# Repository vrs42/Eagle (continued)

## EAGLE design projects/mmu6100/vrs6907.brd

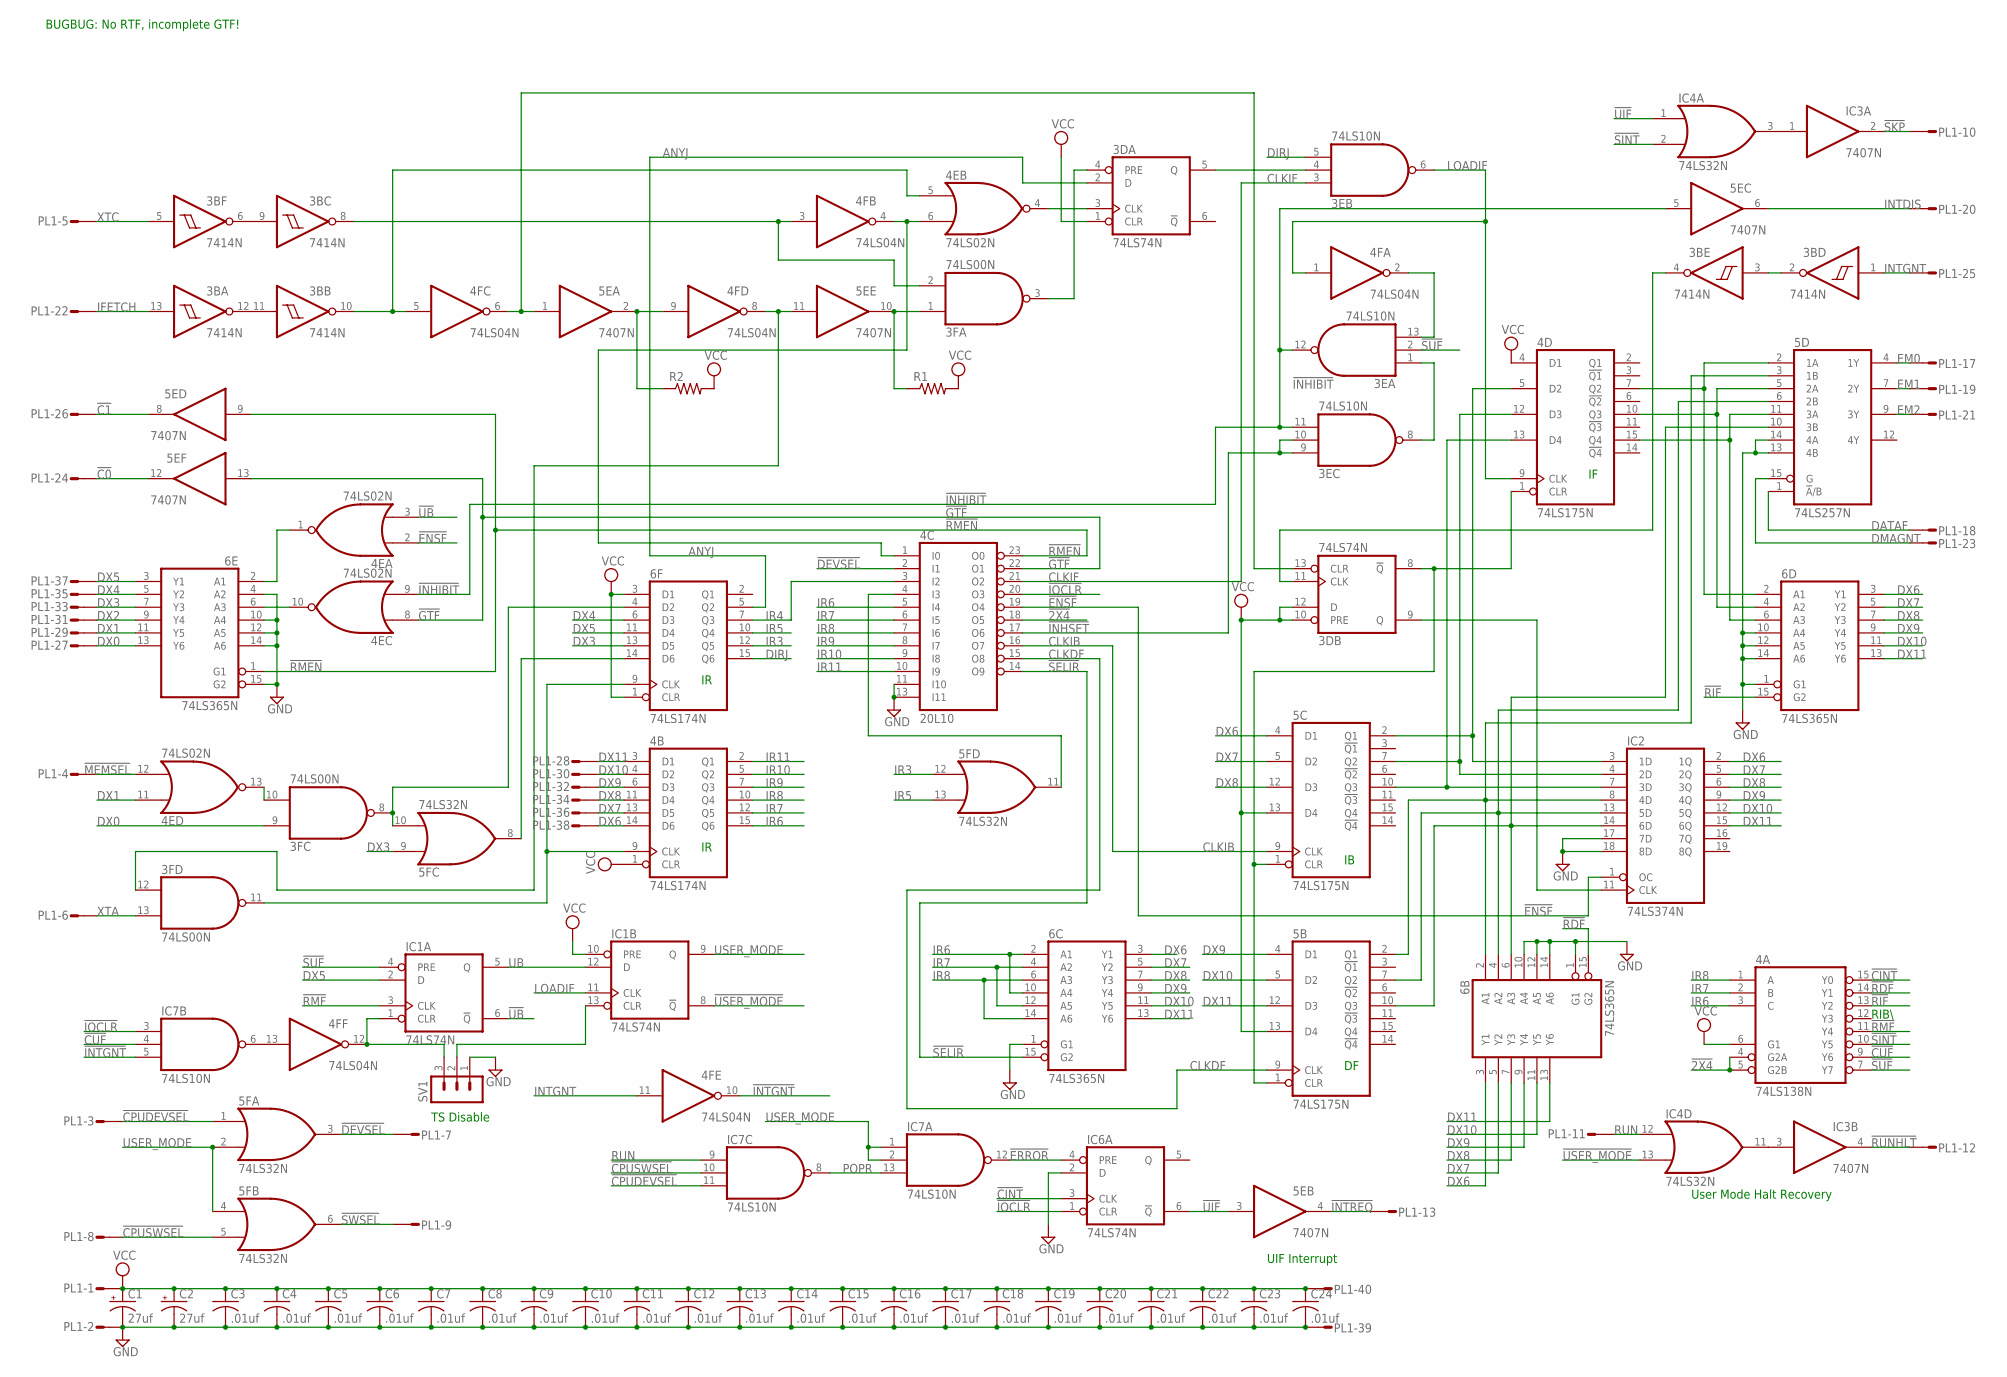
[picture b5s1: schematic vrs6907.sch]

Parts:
3B: 7414N; DIL14
3D: 74LS74N; DIL14
3E: 74LS10N; DIL14
3F: 74LS00N; DIL14
4A: 74LS138N; DIL16
4B, 6F: 74LS174N; DIL16
4C: 20L10; DIL24-3
4D, 5B, 5C: 74LS175N; DIL16
4E: 74LS02N; DIL14
4F: 74LS04N; DIL14
5D: 74LS257N; DIL16
5E: 7407N; DIL14
5F: 74LS32N; DIL14
6B, 6C, 6D, 6E: 74LS365N; DIL16
C1, C2: 27uf; E22-6
C3, C4, C5, C6, C7, C8, C9, C10, C11, C12, C13, C14, C15, C16, C17, C18, C19, C20, C21, C22, C23, C24: .01uf; C050-025X075
IC1, IC6: 74LS74N; DIL14
IC2: 74LS374N; DIL20
IC3: 7407N; DIL14
IC4: 74LS32N; DIL14
IC7: 74LS10N; DIL14
PL1: 40VS; 40V
R1, R2: R-US_0207/10; 0207/10
SV1: MA03-1

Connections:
!2X4: 4A.4 (G2A), 4A.5 (G2B), 4C.18 (O5)
!C0: 5E.12 (O), PL1.24
!C1: 5E.8 (O), PL1.26
!CINT: 4A.15 (Y0), IC6.3 (CLK)
!CPUDEVSEL: 5F.1 (I0), IC7.11 (I2), PL1.3
!CPUSWSEL: 5F.5 (I1), IC7.10 (I1), PL1.8
!CUF: 4A.9 (Y6), IC7.4 (I1)
!DEVSEL: 4C.2 (I1), 5F.3 (O), PL1.7
!ENSF: 4C.19 (O4), 4E.2 (I0), IC2.1 (OC)
!ERROR: IC6.4 (PRE), IC7.12 (O)
!GTF: 4C.22 (O1), 4E.8 (I0), 5E.13 (I)
!INHIBIT: 3E.11 (I2), 3E.12 (O), 4E.9 (I1), 5E.5 (I)
!INHSET: 3E.9 (I0), 3E.10 (I1), 4C.17 (O6)
!INTGNT: 4F.10 (O), IC7.5 (I2)
!INTREQ: 5E.4 (O), PL1.13
!IOCLR: 4C.20 (O3), IC6.1 (CLR), IC7.3 (I0)
!MEMSEL: 4E.12 (I1), PL1.4
!RDF: 4A.14 (Y1), 6B.15 (G2)
!RIF: 4A.13 (Y2), 6D.15 (G2)
!RMEN: 4C.23 (O0), 5E.9 (I), 6E.1 (G1)
!RMF: 4A.11 (Y4), IC1.3 (CLK)
!RUNHLT: IC3.4 (O), PL1.12
!SELIR: 4C.14 (O9), 6C.15 (G2)
!SINT: 4A.10 (Y5), IC4.2 (I1)
!SKP: IC3.2 (O), PL1.10
!SUF: 3E.2 (I1), 4A.7 (Y7), IC1.4 (PRE)
!SWSEL: 5F.6 (O), PL1.9
!UB: 4E.3 (I1), IC1.6 (!Q)
!UIF: 5E.3 (I), IC4.1 (I0), IC6.6 (!Q)
!USER_MODE: IC1.8 (!Q), IC4.13 (I1)
ANYJ: 3D.2 (D), 6F.5 (Q2)
CLKDF: 4C.15 (O8), 5B.9 (CLK)
CLKIB: 4C.16 (O7), 5C.9 (CLK)
CLKIF: 3E.3 (I0), 4C.21 (O2)
DATAF: 5D.1 (!A!/B), PL1.18
DIRJ: 3E.5 (I2), 6F.15 (Q6)
DMAGNT: 5D.15 (G), PL1.23
DX0: 3F.9 (I0), 6E.13 (Y6), PL1.27
DX1: 4E.11 (I0), 6E.11 (Y5), PL1.29
DX2: 6E.9 (Y4), PL1.31
DX3: 5F.9 (I0), 6E.7 (Y3), 6F.13 (D5), PL1.33
DX4: 6E.5 (Y2), 6F.6 (D3), PL1.35
DX5: 6E.3 (Y1), 6F.11 (D4), IC1.2 (D), PL1.37
DX6: 4B.14 (D6), 5C.4 (D1), 6B.3 (Y1), 6C.3 (Y1), 6D.3 (Y1), IC2.2 (1Q), PL1.38
DX7: 4B.13 (D5), 5C.5 (D2), 6B.5 (Y2), 6C.5 (Y2), 6D.5 (Y2), IC2.5 (2Q), PL1.36
DX8: 4B.11 (D4), 5C.12 (D3), 6B.7 (Y3), 6C.7 (Y3), 6D.7 (Y3), IC2.6 (3Q), PL1.34
DX9: 4B.6 (D3), 5B.4 (D1), 6B.9 (Y4), 6C.9 (Y4), 6D.9 (Y4), IC2.9 (4Q), PL1.32
DX10: 4B.4 (D2), 5B.5 (D2), 6B.11 (Y5), 6C.11 (Y5), 6D.11 (Y5), IC2.12 (5Q), PL1.30
DX11: 4B.3 (D1), 5B.12 (D3), 6B.13 (Y6), 6C.13 (Y6), 6D.13 (Y6), IC2.15 (6Q), PL1.28
EM0: 5D.4 (1Y), PL1.17
EM1: 5D.7 (2Y), PL1.19
EM2: 5D.9 (3Y), PL1.21
GND: 3B.7 (GND), 3D.7 (GND), 3E.7 (GND), 3F.7 (GND), 4A.8 (GND), 4B.8 (GND), 4C.11 (I10), 4C.12 (GND), 4C.13 (I11), 4D.8 (GND), 4E.7 (GND), 4F.7 (GND), 5B.8 (GND), 5C.8 (GND), 5D.8 (GND), 5D.13 (4B), 5D.14 (4A), 5E.7 (GND), 5F.7 (GND), 6B.1 (G1), 6B.8 (GND), 6B.10 (A4), 6B.12 (A5), 6B.14 (A6), 6C.1 (G1), 6C.8 (GND), 6D.1 (G1), 6D.8 (GND), 6D.10 (A4), 6D.12 (A5), 6D.14 (A6), 6E.4 (A2), 6E.8 (GND), 6E.10 (A4), 6E.12 (A5), 6E.14 (A6), 6E.15 (G2), 6F.8 (GND), C1.-, C2.-, C3.2, C4.2, C5.2, C6.2, C7.2, C8.2, C9.2, C10.2, C11.2, C12.2, C13.2, C14.2, C15.2, C16.2, C17.2, C18.2, C19.2, C20.2, C21.2, C22.2, C23.2, C24.2, IC1.7 (GND), IC2.10 (GND), IC2.17 (7D), IC2.18 (8D), IC3.7 (GND), IC4.7 (GND), IC6.2 (D), IC6.7 (GND), IC7.7 (GND), PL1.2, PL1.39, SV1.1
IFETCH: 3B.13 (I), PL1.22
INTDIS: 5E.6 (O), PL1.20
INTGNT: 3B.1 (I), 4F.11 (I), PL1.25
IR3: 5F.12 (I0), 6F.12 (Q5)
IR4: 4C.3 (I2), 6F.7 (Q3)
IR5: 5F.13 (I1), 6F.10 (Q4)
IR6: 4A.3 (C), 4B.15 (Q6), 4C.5 (I4), 6C.2 (A1), 6C.10 (A4)
IR7: 4A.2 (B), 4B.12 (Q5), 4C.6 (I5), 6C.4 (A2), 6C.12 (A5)
IR8: 4A.1 (A), 4B.10 (Q4), 4C.7 (I6), 6C.6 (A3), 6C.14 (A6)
IR9: 4B.7 (Q3), 4C.8 (I7)
IR10: 4B.5 (Q2), 4C.9 (I8)
IR11: 4B.2 (Q1), 4C.10 (I9)
LOADIF: 3E.6 (O), 4D.9 (CLK), 4F.1 (I), IC1.11 (CLK)
LOADIR: 3F.11 (O), 4B.9 (CLK), 6F.9 (CLK)
unnamed: 3B.11 (I), 3B.12 (O)
unnamed: 3B.6 (O), 3B.9 (I)
unnamed: 3B.8 (O), 3F.2 (I1), 4F.3 (I)
unnamed: 3B.10 (O), 4E.5 (I0), 4F.5 (I)
unnamed: 3D.13 (CLR), 4F.6 (O), 5E.1 (I)
unnamed: 3D.5 (Q), 3E.4 (I1)
unnamed: 3F.1 (I0), 5E.10 (O), R1.1
unnamed: 3F.12 (I0), 4F.8 (O), 5E.11 (I)
unnamed: 4F.9 (I), 5E.2 (O), R2.1
unnamed: 4C.1 (I0), 4E.6 (I1), 4F.4 (O)
unnamed: 3D.3 (CLK), 4E.4 (O)
unnamed: 3D.4 (PRE), 3F.3 (O)
unnamed: IC3.3 (I), IC4.11 (O)
unnamed: 3F.10 (I1), 4E.13 (O)
unnamed: 4E.10 (O), 6E.6 (A3)
unnamed: 4F.12 (O), IC1.1 (CLR), SV1.3
unnamed: 4E.1 (O), 6E.2 (A1)
unnamed: 3F.8 (O), 5F.10 (I1), 6F.4 (D2)
unnamed: 5F.8 (O), 6F.14 (D6)
unnamed: 4C.4 (I3), 5F.11 (O)
unnamed: IC1.13 (CLR), SV1.2
unnamed: IC3.1 (I), IC4.3 (O)
unnamed: 4F.13 (I), IC7.6 (O)
unnamed: 4D.7 (Q2), 5D.2 (1A), 6D.2 (A1)
unnamed: 4D.15 (Q4), 5D.11 (3A), 6D.6 (A3)
unnamed: 4D.10 (Q3), 5D.5 (2A), 6D.4 (A2)
unnamed: 3D.8 (!Q), 4D.1 (CLR), 5B.1 (CLR), 5C.1 (CLR)
unnamed: 4D.5 (D2), 5C.2 (Q1), IC2.3 (1D)
unnamed: 4D.12 (D3), 5C.7 (Q2), IC2.4 (2D)
unnamed: 4D.13 (D4), 5C.10 (Q3), IC2.7 (3D)
unnamed: 5B.2 (Q1), 5D.3 (1B), 6B.2 (A1), IC2.8 (4D)
unnamed: 5B.7 (Q2), 5D.6 (2B), 6B.4 (A2), IC2.13 (5D)
unnamed: 5B.10 (Q3), 5D.10 (3B), 6B.6 (A3), IC2.14 (6D)
unnamed: 3D.9 (Q), IC2.11 (CLK)
unnamed: 3E.1 (I0), 3E.8 (O)
unnamed: 3E.13 (I2), 4F.2 (O)
unnamed: 3B.2 (O), 3B.3 (I)
unnamed: 3B.4 (O), 3D.11 (CLK)
POPR: IC7.8 (O), IC7.13 (I2)
RUN: IC4.12 (I0), IC7.9 (I0), PL1.11
UB: IC1.5 (Q), IC1.12 (D)
USER_MODE: 5F.2 (I1), 5F.4 (I0), IC1.9 (Q), IC7.1 (I0), IC7.2 (I1)
VCC: 3B.14 (VCC), 3D.1 (CLR), 3D.10 (PRE), 3D.12 (D), 3D.14 (VCC), 3E.14 (VCC), 3F.14 (VCC), 4A.6 (G1), 4A.16 (VCC), 4B.1 (CLR), 4B.16 (VCC), 4C.24 (VCC), 4D.4 (D1), 4D.16 (VCC), 4E.14 (VCC), 4F.14 (VCC), 5B.13 (D4), 5B.16 (VCC), 5C.13 (D4), 5C.16 (VCC), 5D.16 (VCC), 5E.14 (VCC), 5F.14 (VCC), 6B.16 (VCC), 6C.16 (VCC), 6D.16 (VCC), 6E.16 (VCC), 6F.1 (CLR), 6F.3 (D1), 6F.16 (VCC), C1.+, C2.+, C3.1, C4.1, C5.1, C6.1, C7.1, C8.1, C9.1, C10.1, C11.1, C12.1, C13.1, C14.1, C15.1, C16.1, C17.1, C18.1, C19.1, C20.1, C21.1, C22.1, C23.1, C24.1, IC1.10 (PRE), IC1.14 (VCC), IC2.20 (VCC), IC3.14 (VCC), IC4.14 (VCC), IC6.14 (VCC), IC7.14 (VCC), PL1.1, PL1.40, R1.2, R2.2
XTA: 3F.13 (I1), PL1.6
XTC: 3B.5 (I), PL1.5

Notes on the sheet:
UIF Interrupt
User Mode Halt Recovery
RIB\\
TS Disable
BUGBUG: No RTF, incomplete GTF!

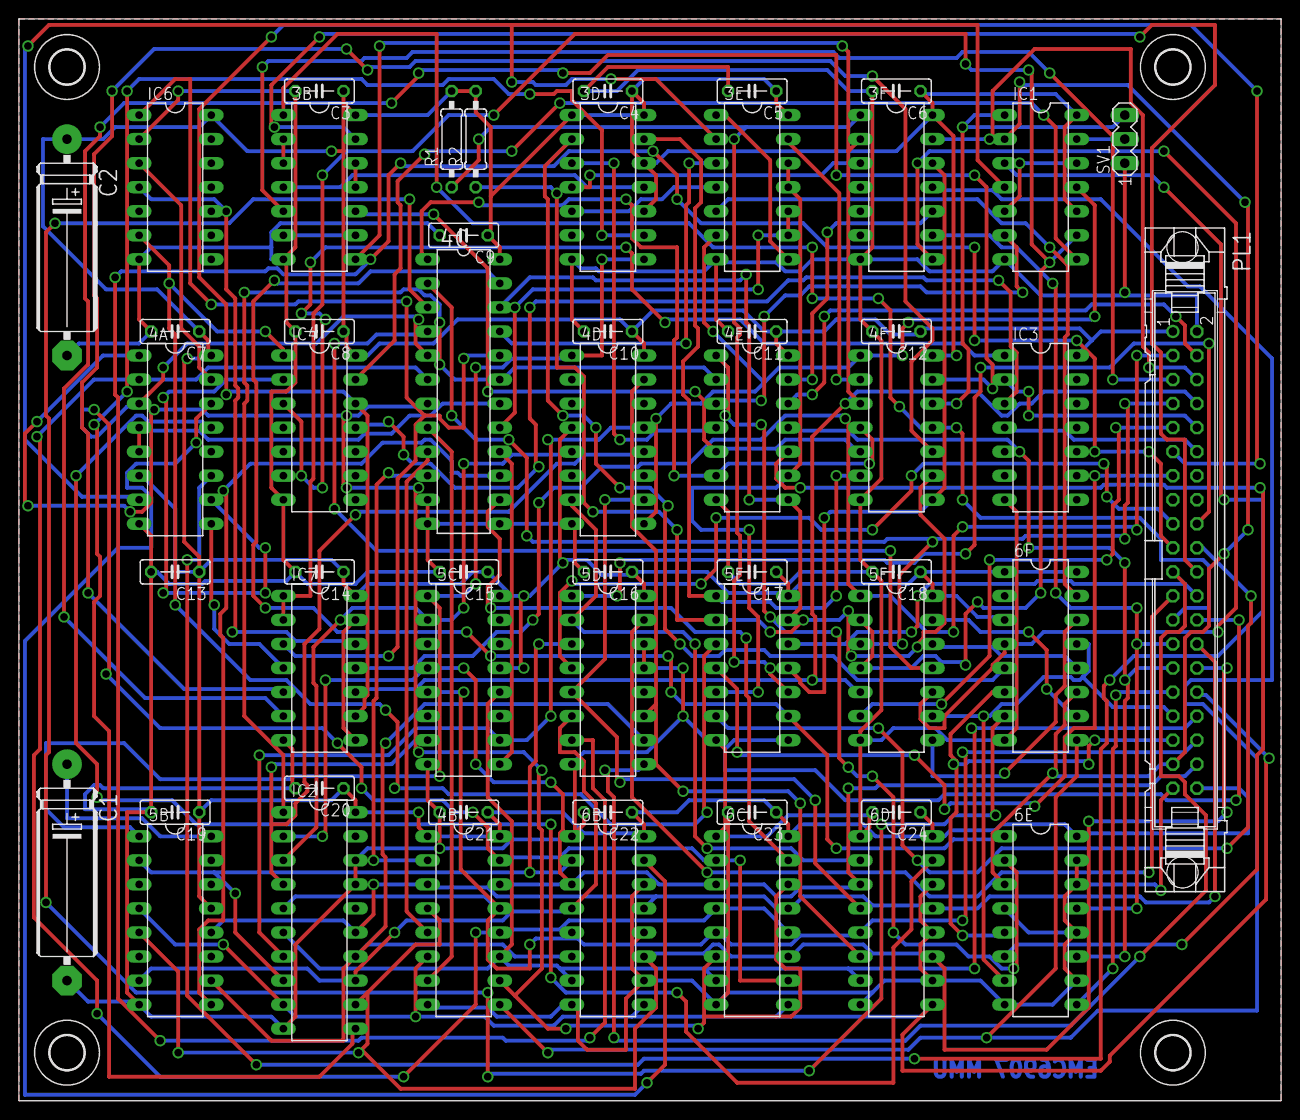
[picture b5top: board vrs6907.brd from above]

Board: 2 copper layers, 133.3 x 114.3 mm, 58 parts (0 on the bottom side), 112 nets.

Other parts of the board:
U$1, U$2, U$3, U$4: 3,6

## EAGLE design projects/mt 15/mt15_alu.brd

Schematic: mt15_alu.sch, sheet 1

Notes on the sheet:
(c) Dieter Müller
2005,2006
1.0
Free for hobby use, but probably not free of errors.
Provided as is , without any warranty or support.
Good luck.
\!A
\!B
\!Q
4:1
Multiplexer
PROPAGATE
Logic Unit
GENERATE
propagate
generate
select
D_IN
from Data_Bus
ALU_A
from Reg.
ACC, PC
\!P
\!G
\!C
\!Y
ALU_Q
Zero
detect
\!P+1
Carry
inverter
...could be improved.
NOTE:
Design is obsolete.
SHR
\!SHR
could be
eliminated.
Random Logic...

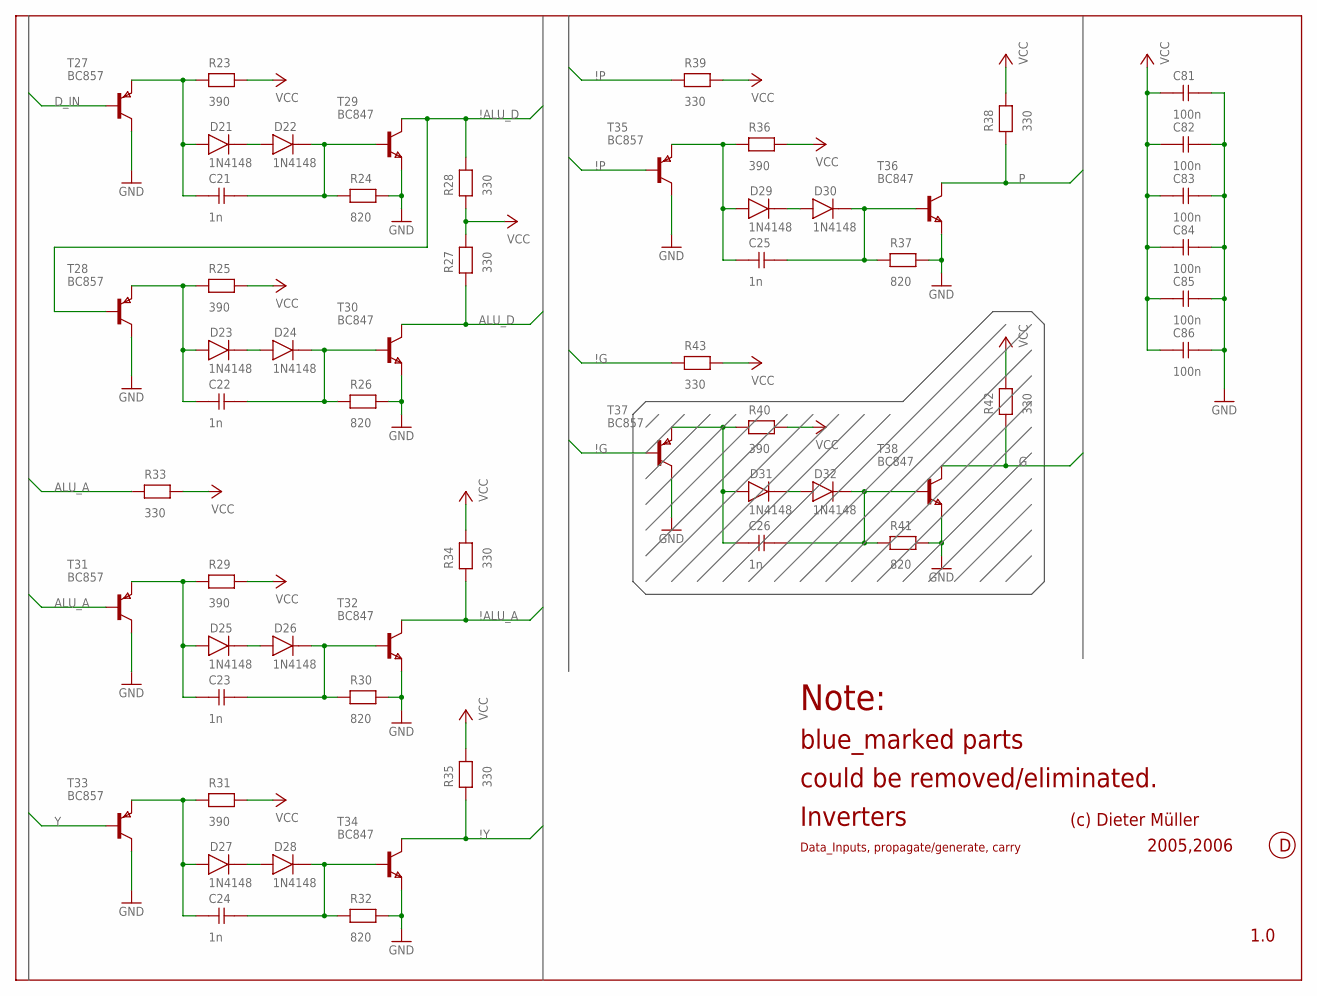
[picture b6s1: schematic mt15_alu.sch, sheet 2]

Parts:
C21, C22, C23, C24, C25, C26: 1n; 0204
C81, C82, C83, C84, C85, C86: 100n; 0204
D21, D22, D23, D24, D25, D26, D27, D28, D29, D30, D31, D32: 1N4148; 0204D
R23, R25, R29, R31, R36, R40: 390; 0204
R24, R26, R30, R32, R37, R41: 820; 0204
R27, R28: 330; 0204@2
R33, R34, R35, R38, R39, R42, R43: 330; 0204
T27, T28, T31, T33, T35, T37: BC857; SOT-23
T29, T30, T32, T34, T36, T38: BC847; SOT-23

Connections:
ALU_A: R33.1, T31.2 (B); also elsewhere on the board
ALU_D: R27.1, T30.3 (C); also elsewhere on the board
D_IN: T27.2 (B)
G: R42.1, T38.3 (C); also elsewhere on the board
GND: C81.2, C82.2, C83.2, C84.2, C85.2, C86.2, R24.2, R26.2, R30.2, R32.2, R37.2, R41.2, T27.3 (C), T28.3 (C), T29.1 (E), T30.1 (E), T31.3 (C), T32.1 (E), T33.3 (C), T34.1 (E), T35.3 (C), T36.1 (E), T37.3 (C), T38.1 (E); also elsewhere on the board
unnamed: C22.1, D23.1 (A), R25.1, T28.1 (E)
unnamed: C21.1, D21.1 (A), R23.1, T27.1 (E)
unnamed: D21.2 (K), D22.1 (A)
unnamed: C21.2, D22.2 (K), R24.1, T29.2 (B)
unnamed: D23.2 (K), D24.1 (A)
unnamed: C22.2, D24.2 (K), R26.1, T30.2 (B)
unnamed: C23.1, D25.1 (A), R29.1, T31.1 (E)
unnamed: D25.2 (K), D26.1 (A)
unnamed: C23.2, D26.2 (K), R30.1, T32.2 (B)
unnamed: C24.1, D27.1 (A), R31.1, T33.1 (E)
unnamed: D27.2 (K), D28.1 (A)
unnamed: C24.2, D28.2 (K), R32.1, T34.2 (B)
unnamed: C25.1, D29.1 (A), R36.1, T35.1 (E)
unnamed: D29.2 (K), D30.1 (A)
unnamed: C25.2, D30.2 (K), R37.1, T36.2 (B)
unnamed: C26.1, D31.1 (A), R40.1, T37.1 (E)
unnamed: D31.2 (K), D32.1 (A)
unnamed: C26.2, D32.2 (K), R41.1, T38.2 (B)
P: R38.1, T36.3 (C); also elsewhere on the board
VCC: C81.1, C82.1, C83.1, C84.1, C85.1, C86.1, R23.2, R25.2, R27.2, R28.1, R29.2, R31.2, R33.2, R34.2, R35.2, R36.2, R38.2, R39.2, R40.2, R42.2, R43.2; also elsewhere on the board
Y: T33.2 (B)
\!ALU_A: R34.1, T32.3 (C); also elsewhere on the board
\!ALU_D: R28.2, T28.2 (B), T29.3 (C); also elsewhere on the board
\!G: R43.1, T37.2 (B); also elsewhere on the board
\!P: R39.1, T35.2 (B); also elsewhere on the board
\!Y: R35.1, T34.3 (C)

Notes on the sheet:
(c) Dieter Müller
2005,2006
1.0
Inverters
Data_Inputs, propagate/generate, carry
Note:
blue_marked parts
could be removed/eliminated.

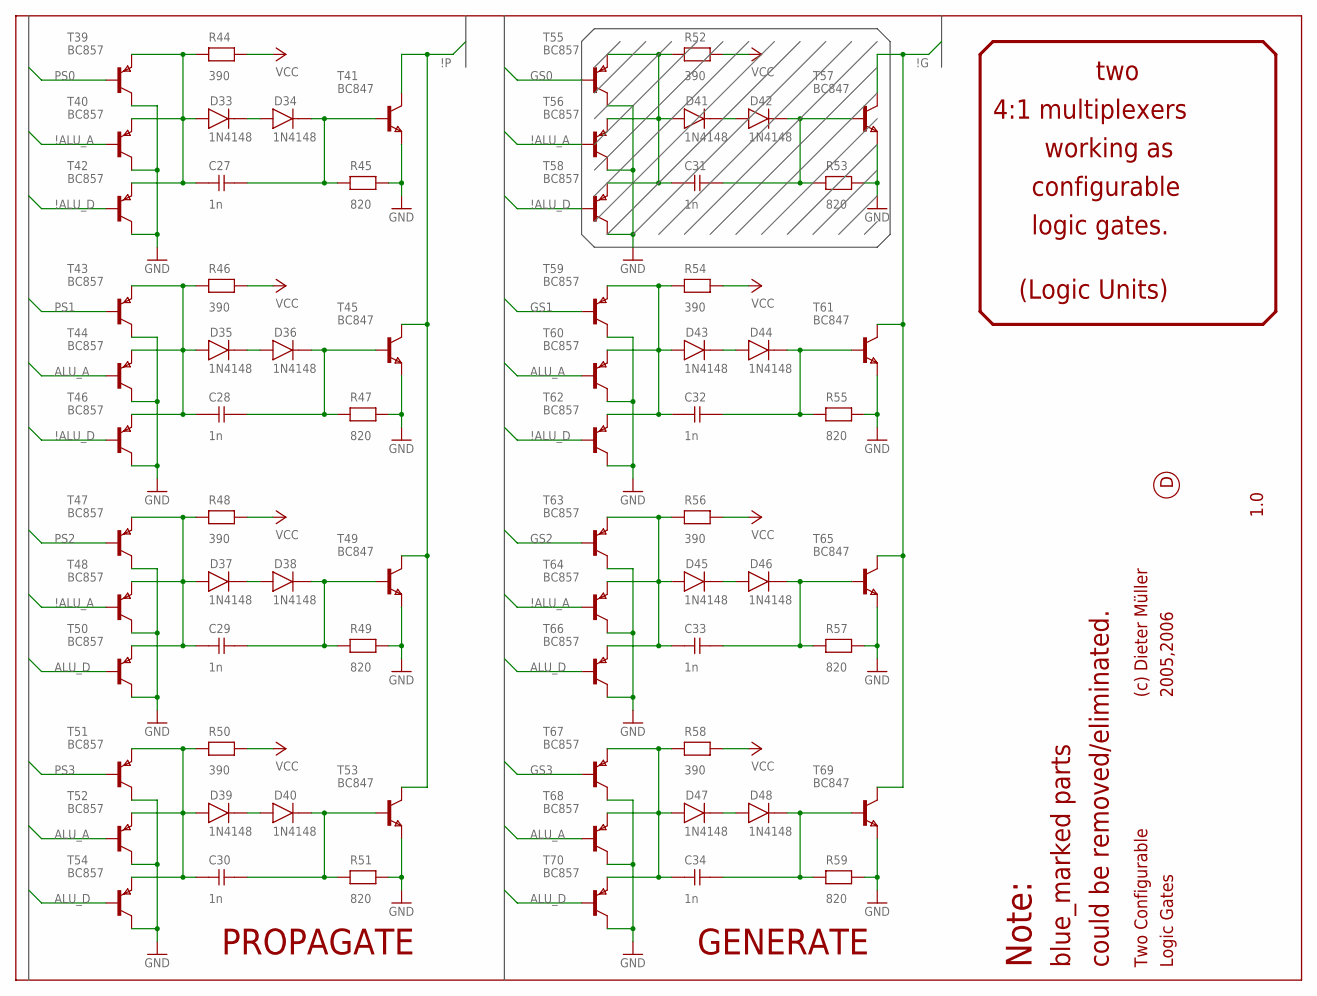
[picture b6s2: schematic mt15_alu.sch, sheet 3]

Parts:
C27, C28, C29, C30, C31, C32, C33, C34: 1n; 0204
D33, D34, D35, D36, D37, D38, D39, D40, D41, D42, D43, D44, D45, D46, D47, D48: 1N4148; 0204D
R44, R46, R48, R50, R52, R54, R56, R58: 390; 0204
R45, R47, R49, R51, R53, R55, R57, R59: 820; 0204
T39, T40, T42, T43, T44, T46, T47, T48, T50, T51, T52, T54, T55, T56, T58, T59, T60, T62, T63, T64, T66, T67, T68, T70: BC857; SOT-23
T41, T45, T49, T53, T57, T61, T65, T69: BC847; SOT-23

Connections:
ALU_A: T44.2 (B), T52.2 (B), T60.2 (B), T68.2 (B); also elsewhere on the board
ALU_D: T50.2 (B), T54.2 (B), T66.2 (B), T70.2 (B); also elsewhere on the board
GND: R45.2, R47.2, R49.2, R51.2, R53.2, R55.2, R57.2, R59.2, T39.3 (C), T40.3 (C), T41.1 (E), T42.3 (C), T43.3 (C), T44.3 (C), T45.1 (E), T46.3 (C), T47.3 (C), T48.3 (C), T49.1 (E), T50.3 (C), T51.3 (C), T52.3 (C), T53.1 (E), T54.3 (C), T55.3 (C), T56.3 (C), T57.1 (E), T58.3 (C), T59.3 (C), T60.3 (C), T61.1 (E), T62.3 (C), T63.3 (C), T64.3 (C), T65.1 (E), T66.3 (C), T67.3 (C), T68.3 (C), T69.1 (E), T70.3 (C); also elsewhere on the board
GS0: T55.2 (B)
GS1: T59.2 (B)
GS2: T63.2 (B)
GS3: T67.2 (B)
unnamed: C27.1, D33.1 (A), R44.1, T39.1 (E), T40.1 (E), T42.1 (E)
unnamed: D33.2 (K), D34.1 (A)
unnamed: C27.2, D34.2 (K), R45.1, T41.2 (B)
unnamed: C28.1, D35.1 (A), R46.1, T43.1 (E), T44.1 (E), T46.1 (E)
unnamed: D35.2 (K), D36.1 (A)
unnamed: C28.2, D36.2 (K), R47.1, T45.2 (B)
unnamed: C29.1, D37.1 (A), R48.1, T47.1 (E), T48.1 (E), T50.1 (E)
unnamed: D37.2 (K), D38.1 (A)
unnamed: C29.2, D38.2 (K), R49.1, T49.2 (B)
unnamed: C30.1, D39.1 (A), R50.1, T51.1 (E), T52.1 (E), T54.1 (E)
unnamed: D39.2 (K), D40.1 (A)
unnamed: C30.2, D40.2 (K), R51.1, T53.2 (B)
unnamed: C31.1, D41.1 (A), R52.1, T55.1 (E), T56.1 (E), T58.1 (E)
unnamed: D41.2 (K), D42.1 (A)
unnamed: C31.2, D42.2 (K), R53.1, T57.2 (B)
unnamed: C32.1, D43.1 (A), R54.1, T59.1 (E), T60.1 (E), T62.1 (E)
unnamed: D43.2 (K), D44.1 (A)
unnamed: C32.2, D44.2 (K), R55.1, T61.2 (B)
unnamed: C33.1, D45.1 (A), R56.1, T63.1 (E), T64.1 (E), T66.1 (E)
unnamed: D45.2 (K), D46.1 (A)
unnamed: C33.2, D46.2 (K), R57.1, T65.2 (B)
unnamed: C34.1, D47.1 (A), R58.1, T67.1 (E), T68.1 (E), T70.1 (E)
unnamed: D47.2 (K), D48.1 (A)
unnamed: C34.2, D48.2 (K), R59.1, T69.2 (B)
PS0: T39.2 (B)
PS1: T43.2 (B)
PS2: T47.2 (B)
PS3: T51.2 (B)
VCC: R44.2, R46.2, R48.2, R50.2, R52.2, R54.2, R56.2, R58.2; also elsewhere on the board
\!ALU_A: T40.2 (B), T48.2 (B), T56.2 (B), T64.2 (B); also elsewhere on the board
\!ALU_D: T42.2 (B), T46.2 (B), T58.2 (B), T62.2 (B); also elsewhere on the board
\!G: T57.3 (C), T61.3 (C), T65.3 (C), T69.3 (C); also elsewhere on the board
\!P: T41.3 (C), T45.3 (C), T49.3 (C), T53.3 (C); also elsewhere on the board

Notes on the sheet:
(c) Dieter Müller
2005,2006
1.0
Two Configurable
Logic Gates
PROPAGATE
GENERATE
Note:
blue_marked parts
could be removed/eliminated.
working as
configurable
logic gates.
(Logic Units)
4:1 multiplexers
two

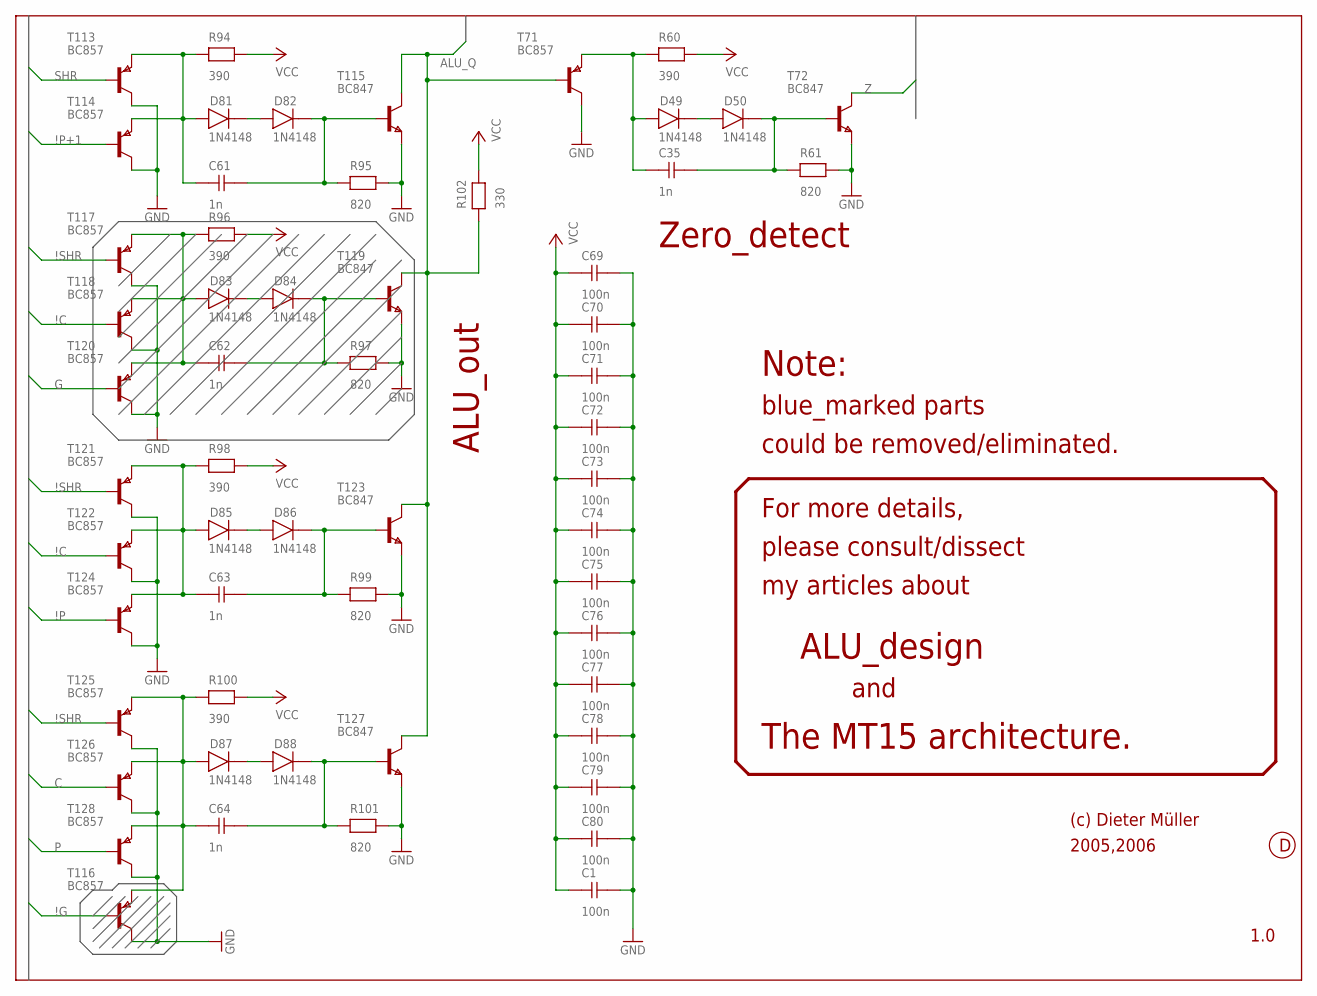
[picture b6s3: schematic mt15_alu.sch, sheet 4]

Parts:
C1, C69, C70, C71, C72, C73, C74, C75, C76, C77, C78, C79, C80: 100n; 0204
C35, C61, C62, C63, C64: 1n; 0204
D49, D50, D81, D82, D83, D84, D85, D86, D87, D88: 1N4148; 0204D
R60, R94, R96, R98, R100: 390; 0204
R61, R95, R97, R99, R101: 820; 0204
R102: 330; 0204
T71, T113, T114, T116, T117, T118, T120, T121, T122, T124, T125, T126, T128: BC857; SOT-23
T72, T115, T119, T123, T127: BC847; SOT-23

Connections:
ALU_Q: R102.1, T71.2 (B), T115.3 (C), T119.3 (C), T123.3 (C), T127.3 (C)
C: T126.2 (B)
G: T120.2 (B); also elsewhere on the board
GND: C1.2, C69.2, C70.2, C71.2, C72.2, C73.2, C74.2, C75.2, C76.2, C77.2, C78.2, C79.2, C80.2, R61.2, R95.2, R97.2, R99.2, R101.2, T71.3 (C), T72.1 (E), T113.3 (C), T114.3 (C), T115.1 (E), T116.3 (C), T117.3 (C), T118.3 (C), T119.1 (E), T120.3 (C), T121.3 (C), T122.3 (C), T123.1 (E), T124.3 (C), T125.3 (C), T126.3 (C), T127.1 (E), T128.3 (C); also elsewhere on the board
unnamed: C35.1, D49.1 (A), R60.1, T71.1 (E)
unnamed: D49.2 (K), D50.1 (A)
unnamed: C61.1, D81.1 (A), R94.1, T113.1 (E), T114.1 (E)
unnamed: D81.2 (K), D82.1 (A)
unnamed: C61.2, D82.2 (K), R95.1, T115.2 (B)
unnamed: C62.1, D83.1 (A), R96.1, T117.1 (E), T118.1 (E), T120.1 (E)
unnamed: D83.2 (K), D84.1 (A)
unnamed: C62.2, D84.2 (K), R97.1, T119.2 (B)
unnamed: C63.1, D85.1 (A), R98.1, T121.1 (E), T122.1 (E), T124.1 (E)
unnamed: D85.2 (K), D86.1 (A)
unnamed: C63.2, D86.2 (K), R99.1, T123.2 (B)
unnamed: C64.1, D87.1 (A), R100.1, T116.1 (E), T125.1 (E), T126.1 (E), T128.1 (E)
unnamed: D87.2 (K), D88.1 (A)
unnamed: C64.2, D88.2 (K), R101.1, T127.2 (B)
unnamed: C35.2, D50.2 (K), R61.1, T72.2 (B)
P: T128.2 (B); also elsewhere on the board
SHR: T113.2 (B)
VCC: C1.1, C69.1, C70.1, C71.1, C72.1, C73.1, C74.1, C75.1, C76.1, C77.1, C78.1, C79.1, C80.1, R60.2, R94.2, R96.2, R98.2, R100.2, R102.2; also elsewhere on the board
Z: T72.3 (C)
\!C: T118.2 (B), T122.2 (B)
\!G: T116.2 (B); also elsewhere on the board
\!P: T124.2 (B); also elsewhere on the board
\!P+1: T114.2 (B)
\!SHR: T117.2 (B), T121.2 (B), T125.2 (B)

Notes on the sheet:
(c) Dieter Müller
2005,2006
1.0
ALU_out
Zero_detect
Note:
blue_marked parts
could be removed/eliminated.
For more details,
please consult/dissect
my articles about
ALU_design
and
The MT15 architecture.

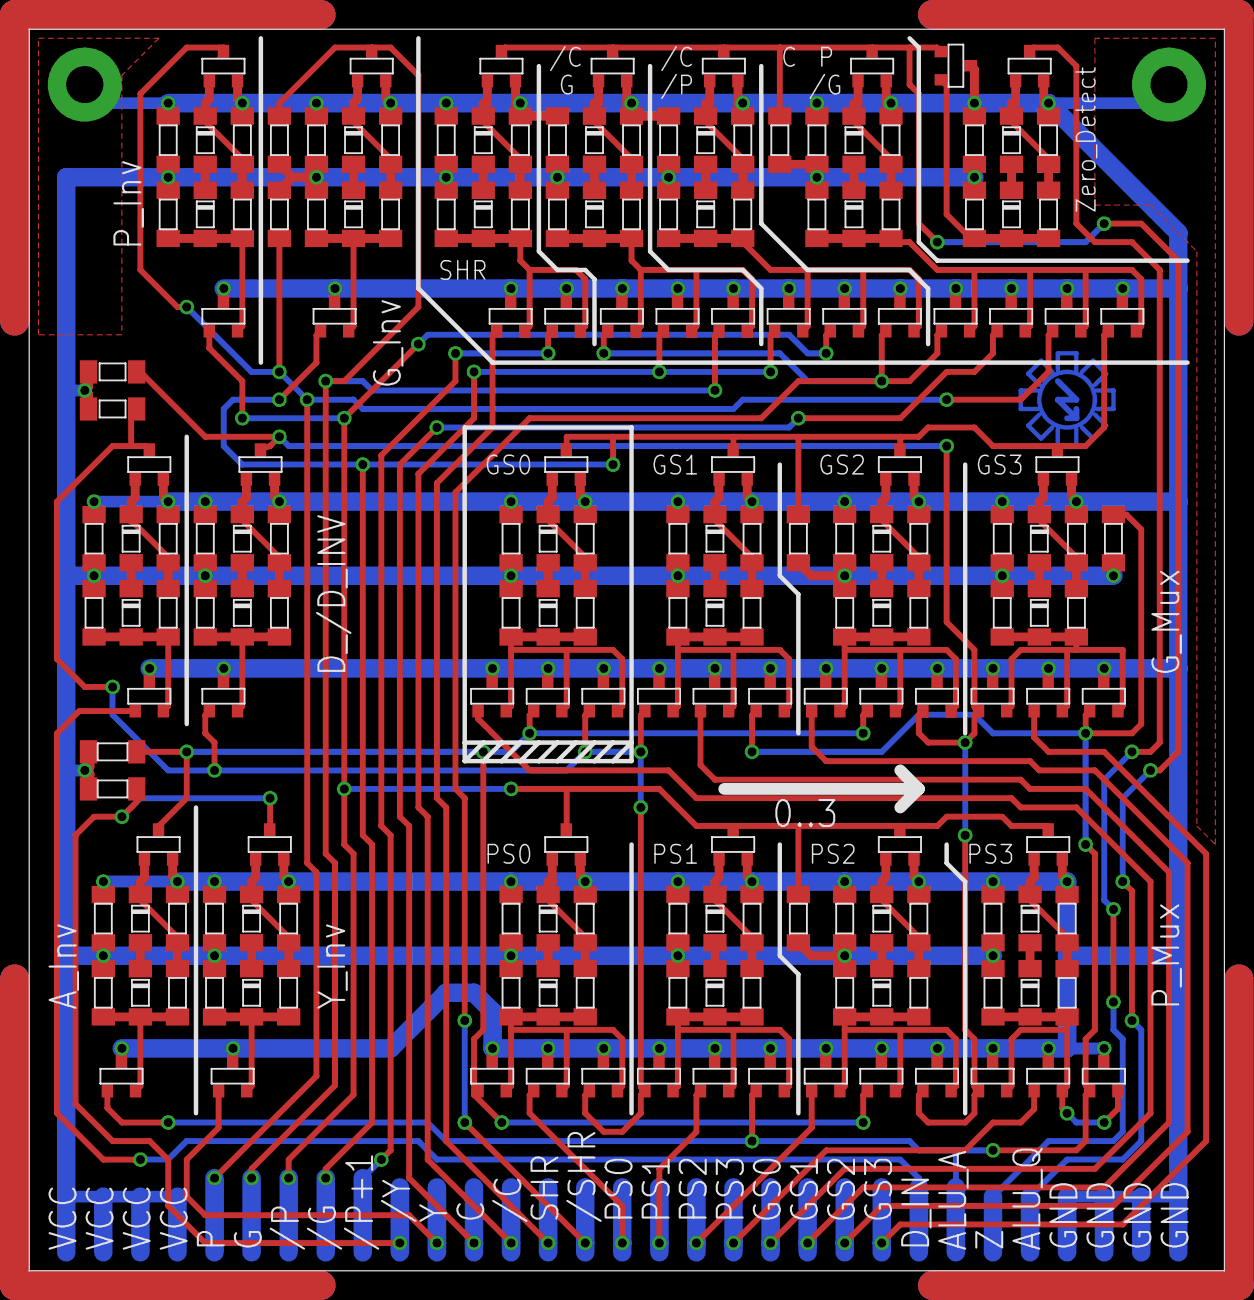
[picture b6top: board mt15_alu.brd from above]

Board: 2 copper layers, 81.9 x 85.1 mm, 187 parts (1 on the bottom side), 71 nets.

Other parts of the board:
U$1: T1

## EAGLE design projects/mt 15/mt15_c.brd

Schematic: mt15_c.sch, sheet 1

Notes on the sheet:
\!P2
\!P1
\!P0
\!C0
\!G0
\!C3
\!C2
\!C1
\!G1
\!G2
\!G3
\!P3
\!G
\!P
(c) Dieter Müller
Block Diagram
Free for hobby use, but probably not free of errors.
Provided as is , without any warranty or support.
Good luck.
2005,2006
1.0
4 Bit
Parallel Carry
Module
basically a
74S182
equivalent
in CTL logic.
(gates have
open Emitter
WARNING:
VCC = 2.5V
change/modify resistors
for other supply voltages.
outputs)
logic equivalent
Wenn dich jemand dann und wann,
grundlos plötzlich lächelt an.
Wenn sie Interesse heucheln,
hinterrücks danach dich meucheln.

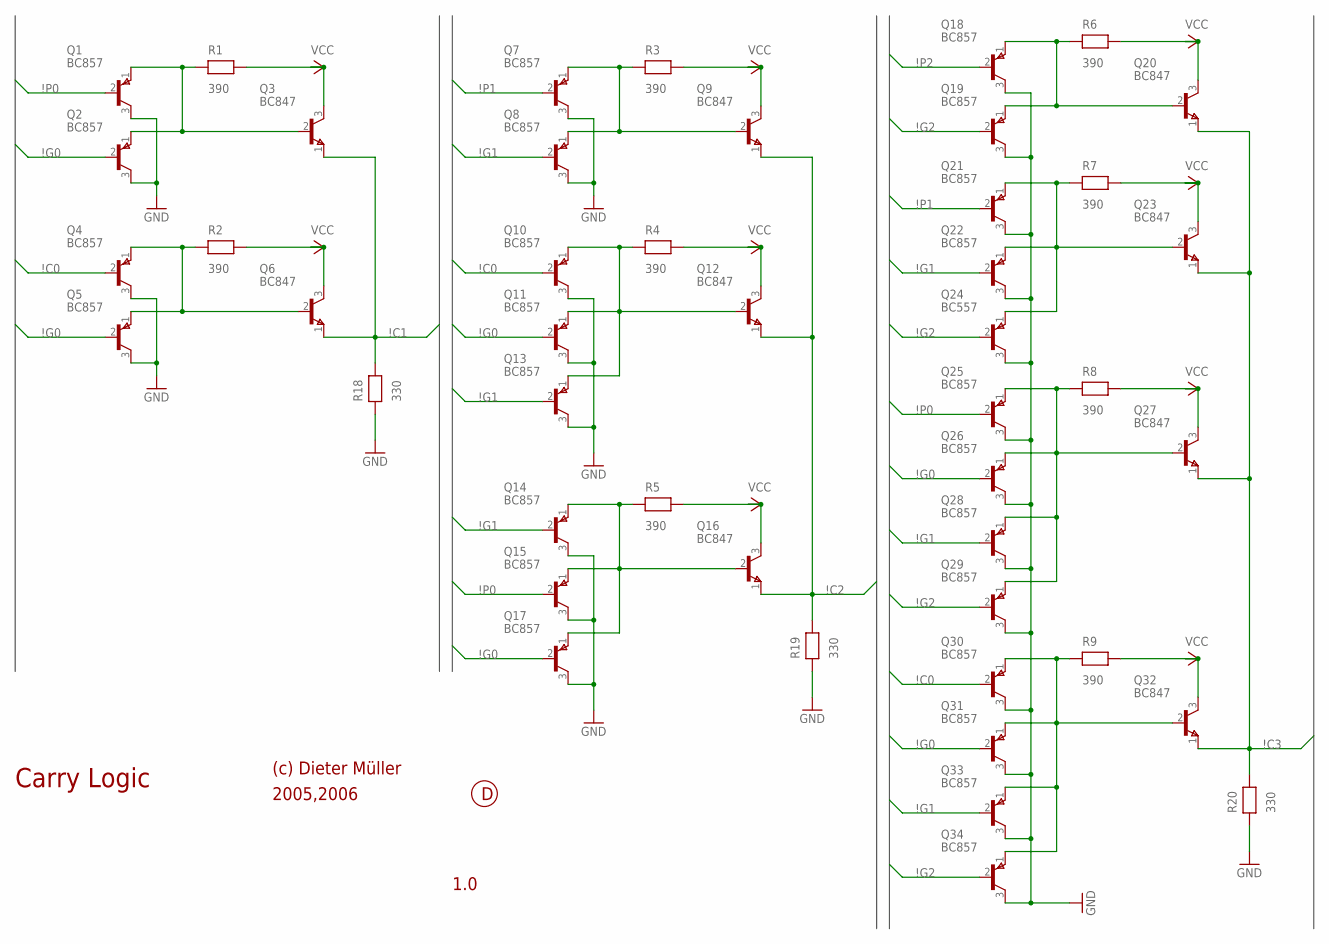
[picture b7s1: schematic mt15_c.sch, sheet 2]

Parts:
Q1, Q2, Q4, Q5, Q7, Q8, Q10, Q11, Q13, Q14, Q15, Q17, Q18, Q19, Q21, Q22, Q25, Q26, Q28, Q29, Q30, Q31, Q33, Q34: BC857; SOT-23
Q3, Q6, Q9, Q12, Q16, Q20, Q23, Q27, Q32: BC847; SOT-23
Q24: BC557; SOT-23
R1, R2, R3, R4, R5, R6, R7, R8, R9: 390; 0204
R18, R19, R20: 330; 0204

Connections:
GND: Q1.3 (C), Q2.3 (C), Q4.3 (C), Q5.3 (C), Q7.3 (C), Q8.3 (C), Q10.3 (C), Q11.3 (C), Q13.3 (C), Q14.3 (C), Q15.3 (C), Q17.3 (C), Q18.3 (C), Q19.3 (C), Q21.3 (C), Q22.3 (C), Q24.3 (C), Q25.3 (C), Q26.3 (C), Q28.3 (C), Q29.3 (C), Q30.3 (C), Q31.3 (C), Q33.3 (C), Q34.3 (C), R18.1, R19.1, R20.1; also elsewhere on the board
unnamed: Q1.1 (E), Q2.1 (E), Q3.2 (B), R1.1
unnamed: Q7.1 (E), Q8.1 (E), Q9.2 (B), R3.1
unnamed: Q4.1 (E), Q5.1 (E), Q6.2 (B), R2.1
unnamed: Q10.1 (E), Q11.1 (E), Q12.2 (B), Q13.1 (E), R4.1
unnamed: Q14.1 (E), Q15.1 (E), Q16.2 (B), Q17.1 (E), R5.1
unnamed: Q18.1 (E), Q19.1 (E), Q20.2 (B), R6.1
unnamed: Q21.1 (E), Q22.1 (E), Q23.2 (B), Q24.1 (E), R7.1
unnamed: Q25.1 (E), Q26.1 (E), Q27.2 (B), Q28.1 (E), Q29.1 (E), R8.1
unnamed: Q30.1 (E), Q31.1 (E), Q32.2 (B), Q33.1 (E), Q34.1 (E), R9.1
VCC: Q3.3 (C), Q6.3 (C), Q9.3 (C), Q12.3 (C), Q16.3 (C), Q20.3 (C), Q23.3 (C), Q27.3 (C), Q32.3 (C), R1.2, R2.2, R3.2, R4.2, R5.2, R6.2, R7.2, R8.2, R9.2; also elsewhere on the board
\!C0: Q4.2 (B), Q10.2 (B), Q30.2 (B)
\!C1: Q3.1 (E), Q6.1 (E), R18.2
\!C2: Q9.1 (E), Q12.1 (E), Q16.1 (E), R19.2
\!C3: Q20.1 (E), Q23.1 (E), Q27.1 (E), Q32.1 (E), R20.2
\!G0: Q2.2 (B), Q5.2 (B), Q11.2 (B), Q17.2 (B), Q26.2 (B), Q31.2 (B); also elsewhere on the board
\!G1: Q8.2 (B), Q13.2 (B), Q14.2 (B), Q22.2 (B), Q28.2 (B), Q33.2 (B); also elsewhere on the board
\!G2: Q19.2 (B), Q24.2 (B), Q29.2 (B), Q34.2 (B); also elsewhere on the board
\!P0: Q1.2 (B), Q15.2 (B), Q25.2 (B); also elsewhere on the board
\!P1: Q7.2 (B), Q21.2 (B); also elsewhere on the board
\!P2: Q18.2 (B); also elsewhere on the board

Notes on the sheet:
(c) Dieter Müller
2005,2006
1.0
Carry Logic
